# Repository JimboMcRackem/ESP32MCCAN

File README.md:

# ESP32 MCCAN

ESP32 motorcycle lighting controller. It reads the bike's CAN bus and drives 12 on/off outputs.
You configure it from a phone over its own Wi-Fi network.

The firmware is one image. `tools/embed_web.py` embeds the web app from `data/` at build time,
so there is no separate filesystem flash.

Settings and the Wi-Fi password live in NVS (namespace `mccan`). A legacy `/config.json` is
migrated once and then deleted, but only on a unit that still has the old partition table (see
below).

## Flashing over USB

Before the first USB flash of this firmware:

1. `python -m pip install cryptography` (needed by `tools/sign_update.py`).
2. `python tools/sign_update.py keygen`, then commit `src/domain/update_pubkey.h`. Firmware built
   with the all-zero placeholder key refuses every phone update until it is flashed over USB
   again.
3. Export your settings from the app's Backup tab. This firmware uses the `min_spiffs.csv`
   partition table (bigger app slots), so the old `/config.json` is not carried over. Import the
   backup after flashing.

```
PYTHONIOENCODING=utf-8 py -3.13 -m platformio run -e esp32 -t upload
```

This is the only flash. There is no `uploadfs`. Native tests run with `python -m platformio test -e native`.

The controller's Wi-Fi network is `MCCAN-XXXX` (XXXX is the last two bytes of the SoftAP MAC
address, which differs from the base MAC printed on module labels).
The default password is `mccan1234`, and the app nags until you change it.

## Releasing an update

1. Once only, before the first USB flash: `python tools/sign_update.py keygen`. The private key goes to `~/.mccan/update_key.pem`
   and the public half to `src/domain/update_pubkey.h`, which is built into the firmware.
   **Back up the key.** If it is lost, units in the field can only be updated over USB.
2. Bump `kBuildNumber` and `kVersionString` in `src/version.h`.
3. Build: `PYTHONIOENCODING=utf-8 py -3.13 -m platformio run -e esp32`
4. Sign:
   ```
   python tools/sign_update.py sign --key ~/.mccan/update_key.pem --bin .pio/build/esp32/firmware.bin --out mccan-<version>.mcup
   ```

The `.mcup` format is documented at the top of `tools/sign_update.py`.

## Installing an update from the phone

1. Join the `MCCAN-XXXX` network and open the app.
2. Go to the Device tab and choose the `.mcup` file.
3. The controller refuses an older build, and refuses any update while the bike is not parked.
4. After the update it restarts once the bike reads parked. The new image marks itself good
   after it has run for about 5 s with the Wi-Fi network up. If it crashes or is power-cycled
   before that, the next start goes back to the previous image. An image that hangs stays until
   a power cycle, and one that runs but behaves wrongly is kept: install a fixed update.

## Recovering a forgotten password

Factory reset: hold the reset button (GPIO0, labelled BOOT on the dev board) for 10 s while the
controller is running, then **release it within 5 s**. That erases the settings, and the
controller restarts with defaults (password `mccan1234`) as soon as the bike reads parked. A short
press does nothing. If the button is still held 5 s after the 10 s mark, the reset is cancelled;
release it and start a new 10 s hold to try again. The lamps keep working throughout.

Feedback: on the MCCAN board the status LED (GPIO13) fast-blinks at the 10 s mark (release now),
goes solid once the settings are erased, and goes off if cancelled. The dev board has no LED on
GPIO13: watch the serial log instead (`reset button held 10 s: release within 5 s ...`,
`factory reset: settings erased`).

Holding the button at power-up enters the ESP32's USB flashing mode instead. That is harmless.

## Bring-up notes

- On the dev board, a serial terminal that asserts DTR without RTS can hold GPIO0 low through the
  auto-program circuit. Held, it arms the reset at 10 s and cancels it at 15 s; it never erases
  unless the line is released inside that window. Use a monitor that leaves DTR and RTS
  deasserted.
- Hold BOOT through "Connecting......" if the upload cannot connect.

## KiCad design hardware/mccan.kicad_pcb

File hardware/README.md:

# MCCAN Hardware

KiCad 10.0.2 project for the ESP32 MCCAN lighting controller.
Spec: `../docs/superpowers/specs/2026-10-17-emarked-module-redesign-design.md`
Plan: `../docs/superpowers/plans/2026-10-18-board-schematic-phase-a.md`

## kicad-cli is not on PATH

Bash:       "/c/Program Files/KiCad/10.0/bin/kicad-cli.exe" <args>
PowerShell: & "C:\Program Files\KiCad\10.0\bin\kicad-cli.exe" <args>

## Verification gates

ERC applies to the current schematic. The DRC commands below apply to the abandoned plan3 board
until the layout phase produces a new one.

ERC (must exit 0):
  "/c/Program Files/KiCad/10.0/bin/kicad-cli.exe" sch erc \
    --severity-error --exit-code-violations \
    -o output/erc.rpt mccan.kicad_sch

DRC — run BOTH severities, and read the counts in the report body, not the exit code:

  "/c/Program Files/KiCad/10.0/bin/kicad-cli.exe" pcb drc \
    --severity-error --schematic-parity --exit-code-violations \
    --refill-zones -o output/drc.rpt mccan.kicad_pcb

  "/c/Program Files/KiCad/10.0/bin/kicad-cli.exe" pcb drc \
    --severity-all --schematic-parity --exit-code-violations \
    --refill-zones -o output/drc-all.rpt mccan.kicad_pcb

`--severity-error` alone is NOT the gate, and was the whole of it until Task 10. It discards
every finding whose rule sits at `warning`, and KiCad's stock project file puts 29 of its 62
rules there. On the board committed before `80fe282` that gate printed "Found 0 violations"
while `--severity-all` printed 28 — 15 `connection_width` and 13 `via_dangling`, one of the
`connection_width` findings a 0.059 mm neck at an eFuse gate pad. Every "DRC: 0 errors" on
this branch before that commit was measured through that filter.

`scripts/gen_netclasses.py` now promotes the seven rules that can fail THIS board to `error`
(see its `SEVERITIES`), so today the two runs agree. That agreement is a property of the
current KiCad rule set, not of the gate: a KiCad upgrade that adds a rule defaulting to
`warning` would make the `--severity-error` run blind again with no signal at all. Hence both.

Neither run's exit code is the pass/fail signal on its own — `kicad-cli` exits 5 whenever any
unconnected pad exists, and this board carries 11 accepted ones. The gate is the count in the
report body: it must match the accepted residual, currently 9 violations (all `via_dangling`),
11 unconnected pads, 0 footprint errors, at BOTH severities.

## Board setup decisions

Minimum connection width is 0.20 mm, tied to minimum track width.

  This section used to read "0.15 mm, not 0.25 mm ... minimum track width stays 0.25 mm",
  which was the six-layer board's setting and is three wrong figures now: both rules are
  0.20 mm today (`scripts/gen_netclasses.py`'s `RULES`, and `mccan.kicad_pro`).

  The two ARE tied on purpose. min_connection is the narrowest copper that may carry a
  connection, so setting it above the thinnest track the board permits makes every
  legitimately necked track a violation of a rule the same file grants -- two 0.20 mm
  tracks meeting at 45 degrees neck to 0.20 * cos(22.5) = 0.185 mm at the joint. The
  earlier note reached for the fabricator's limit instead, which is what the SCOPED
  plane-pour exception in `mccan.kicad_dru` is for, not what this rule is for. See the
  long `min_connection` note in `scripts/gen_netclasses.py`.

Reference designators are on F.Fab, except J*, F*, TP*, U*, Q*, D* and L*.

  233 parts on 140 x 100 mm leaves no room for 1 mm text: all 398 silkscreen warnings were
  Reference fields over a pad, over a neighbour's outline, or over another Reference, and
  none was between two real silk graphics.  Value was already on F.Fab, so the assembly
  drawing carries a fully labelled copy either way.  What stays on the silkscreen is what
  someone has to find on a finished board by eye -- connectors, fuses, test points and the
  semiconductors worth probing -- plus the outlines, pin-1 dots and polarity marks.

## Sheet responsibilities

| Sheet | Contents |
|---|---|
| power_input | Feed A (J1): LTC4380 U10 surge stopper with Q10/Q11 (no board fuse; the fuse is in the harness), 24 V TVS, pi + CM filter -> `VBAT`. Feed B (J9): SQJ461EP P-FET Q13 for reverse polarity, 15 V gate zener D24, 24 V TVS D25 -> `VBAT_B`, no filter, no LTC4380. `GND_B` (also the pods' return, out to the outputs sheet) meets `GND_IN` (the connector side of choke L2) only at net-tie NT1, so neither feed's return current bypasses L2's return winding |
| rails | Low-Iq buck -> `+3V3_ALW`, gated `+5V` (`EN_5V`). No boost and no `+3V3_SW` |
| mcu_can | ESP32-WROOM-32E, TJA1042T/3 (listen-only, TXD pulled up, no MCU link), programming header, 4.7 k series resistors on the diagnostic lines. GPIO 13 is `AUX_PWM` (the status LED is gone, 2026-11-13) |
| outputs | Three TPS4H160-Q1 quads U11-U13 (D1: 12 channels, 10 used, 2 spare), harness tails J3 (front, 5), J4 + J5 (rear, 4 + 3), CAN tail J8. Aux stage (2026-11-13): BTS7008-2EPA U14 switches both pods from `VBAT_B`, 74AHCT2G126DC U15 buffers `AUX_PWM` to each yellow (enabled only while that pod is powered), pod tails J10/J11. See `docs/superpowers/specs/2026-11-13-aux-stage-design.md` |

The pin map and net names are the generators' (`scripts/gen_*.py`, `scripts/quadpins.py`) and the
netlist `output/netlist.net`. The plan3 pin tables that used to be here (PCA9685, mux, ignition
sense, PWM nets) described a board that no longer exists and have been removed.

### ESP32 pin rules that still hold

- GPIO 6-11 are the module's flash and are unusable. GPIO 37 and 38 are not bonded out.
- GPIO 34-39 are input-only and have **no internal pulls**. Here: 34 `SNS_A`, 35 `CAN_RXD`
  (RTC, EXT1 wake), 36 `SNS_B`, 39 `SNS_C`.
- ADC2 fails while Wi-Fi is up, so the sense inputs are all ADC1.
- Strapping pins, and what this board ties them to:
  - GPIO 0 is `BOOT_N`: the BOOT button SW1 and the auto-reset transistor Q3.
  - GPIO 2 is `DIAG_EN`: 4.7 k series, with R33 47 k pull-down on the chip side. It must be low
    for download, and the same pull-down holds the switches' `DIAG_EN` low. High level: 47 k ∥ 33.3 k
    (three chips at 100 k min) = 19.5 k, so 3.3 × 19.5 / (19.5 + 4.7) = 2.66 V against VIH 2.0 V.
  - GPIO 5 and 15 are `DIAG_SEL0` / `DIAG_SEL1`: 4.7 k series, **no pull** (their level is
    irrelevant while `DIAG_EN` is low). The three SEH internal pull-downs (100 k min each) load
    GPIO 15 against its internal pull-up, so the ROM boot log will probably be muted; that is
    harmless. Optional fix: a 10 k pull-up on the MCU side of R32 (not fitted).
  - GPIO 12 is `IO12_STRAP`: R36 10 k to GND (flash voltage select; also the firmware's TWAI TX pin).
- No lamp output sits on a strapping pin or on GPIO 14.

## Phase-A board status (2026-10-18)

The **schematic** is complete except the kit-gated aux/pod switch. The **layout has not started**.

- `mccan.kicad_pcb` and `output/gerbers/` are the **abandoned plan3 board**. They no longer match
  the schematic and must not be fabricated or used as a layout starting point. The DRC commands
  and counts under "Verification gates" describe that board.
- `scripts/layout_*.py` and `scripts/route_*` (also `routes_signal.json`) still reference plan3
  parts that phase A deleted -- `layout_pcb.py` lists refs such as U7, U8, U9, J6 and J7 -- and
  must be reworked in the layout phase. Do not run them, or `gen_pcb.py`, until then.

### Layout-phase notes

- **U10 (LTC4380) `ON` is deliberately left open** on its internal 1 Mohm pull-up. The layout must
  keep that pin's leakage to ground under 1 uA (LTC4380 Rev. C, Pin Functions): no flux-prone
  gap, guard or close ground copper beside the pad.
- `NT1` is the deliberate `GND_B` / `GND_IN` star point (connector side of L2, so no return current bypasses L2's return winding); place it deliberately (spec §4.1.1). It is a 2.0 mm tie so it outlasts the harness fuse when one feed is reversed while the other is connected.

### Phase-A bring-up checklist (additions)

- **ROM boot log may be absent.** The three SEH internal pull-downs load GPIO 15 (MTDO), so the boot ROM log is probably muted. Harmless. Optional fix: a 10 k pull-up on the MCU side of R32 (not fitted).
- **GPIO12 / flash voltage.** TWAI holds GPIO12 (the MTDI strap) high while running. R36 makes every reset safe. The optional permanent remedy is `espefuse.py set_flash_voltage 3.3V`, which is **IRREVERSIBLE** and is the owner's decision; it has not been run.
- **Diagnostics settling.** After any `DIAG_SEL` or `DIAG_EN` change wait >= 400 us before reading `SNS_x`.
- **Reverse polarity.** Test one feed reversed with the other disconnected, and the whole harness reversed. Test one feed reversed with the other connected only on a current-limited bench supply: that drives fault current through NT1 and the shared return until the harness fuse clears.
- `R100` sets about 9 A behind a 4 A fuse and is re-sized once pod inrush is measured (spec §9.1 item 2a).

> The two sections below, "Project status (Task 1)" and the 2026-09-11 revision, are plan3 history
> kept for the record; the phase-A status above supersedes them.

## Project status (Task 1)

Hierarchical sheets ARE wired: the root schematic (`mccan.kicad_sch`) places four
`(sheet ...)` instances (`power_input`, `rails`, `mcu_can`, `outputs`), each pointing at
its file under `sheets/`. This was authored as text — no KiCad GUI session was available —
and verified structurally sound by running `kicad-cli sch erc`, whose report walked into
all four child sheets (`Sheet /power_input/`, `Sheet /mcu_can/`, `Sheet /rails/`,
`Sheet /outputs/`) with 0 errors. No components are placed on any sheet yet; that begins
in Task 3.

There is no `mccan.kicad_pcb` yet, so the DRC gate above cannot be run until PCB layout
(Task 8) creates one. The command is documented here now because the net naming and
sheet contracts it will check are fixed as of this task.

## Verified gate: ERC (Task 1, empty project)

Command:
```
cd hardware && "/c/Program Files/KiCad/10.0/bin/kicad-cli.exe" sch erc \
  --severity-error --exit-code-violations -o output/erc.rpt mccan.kicad_sch
```

Result: `exit=0`, "Found 0 violations". Report saved at `output/erc.rpt`. This is expected
at this stage — it proves the gate command and the hierarchical project structure work,
not that any design is correct (there is no design yet).

## REVISION 2026-09-11 — RGB output stage redesigned

Datasheet verification failed the octal smart low-side switches: ON-state open-load detection does
not exist in that part category (TLE8110ED's open-load code is OFF-mode only, and it is a VDS
comparator with no load-current threshold at all). The RGB stage is now:

- **12 discrete logic-level N-MOSFETs**, gates driven straight from PCA9685 LED0-11
- **1 ohm shunt in each FET source leg** -> 12 `SENSE_*` nets
- **16:1 analog mux** (`MUX_S0`-`S3`) -> `RGB_ISNS` -> GPIO 32 (ADC1_CH4)
- 140 mV at full channel current; ADC at 0 dB attenuation (0-1.1 V range)
- Classification is open / working / shorted, not precision metering
- Sampling is on-demand: drive a channel to 100%, step the mux, read, advance

**There is no SPI on this board** — the switch ICs were its only devices. Dropping it freed the
GPIO that made the sense chain fit.

**A 5 V rail is mandatory**: TJA1042 VCC is 4.5-5.5 V. The "/3" suffix provides VIO for 3.3 V logic
levels; it does not make VCC 3.3 V. **It is ENABLE-GATED off in sleep**, sharing `EN_3V3SW` with
`+3V3_SW` — the transceiver's low-power receiver detects bus activity on **VIO alone**, so VCC is
needed only for normal mode. VIO stays on `+3V3_ALW`.

Authority: `../docs/superpowers/specs/2026-09-11-esp32-mccan-pcb-hardware-design.md` sections 5.1,
6 and 7.3.

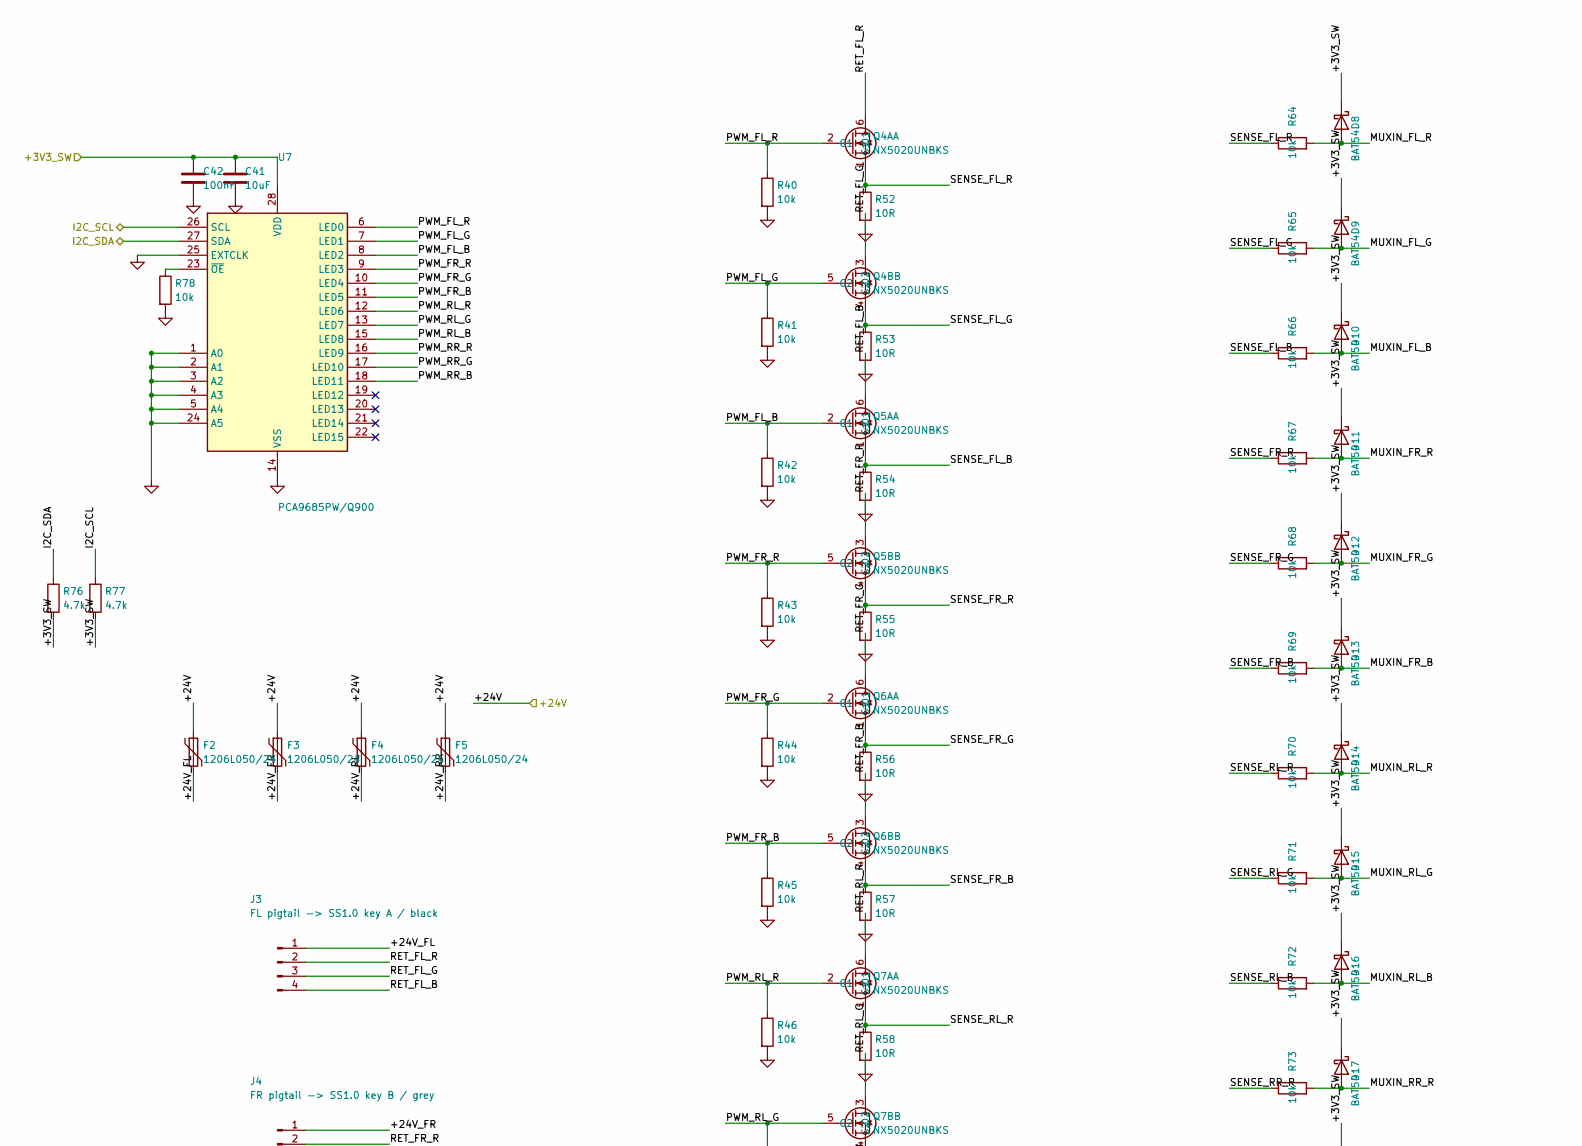
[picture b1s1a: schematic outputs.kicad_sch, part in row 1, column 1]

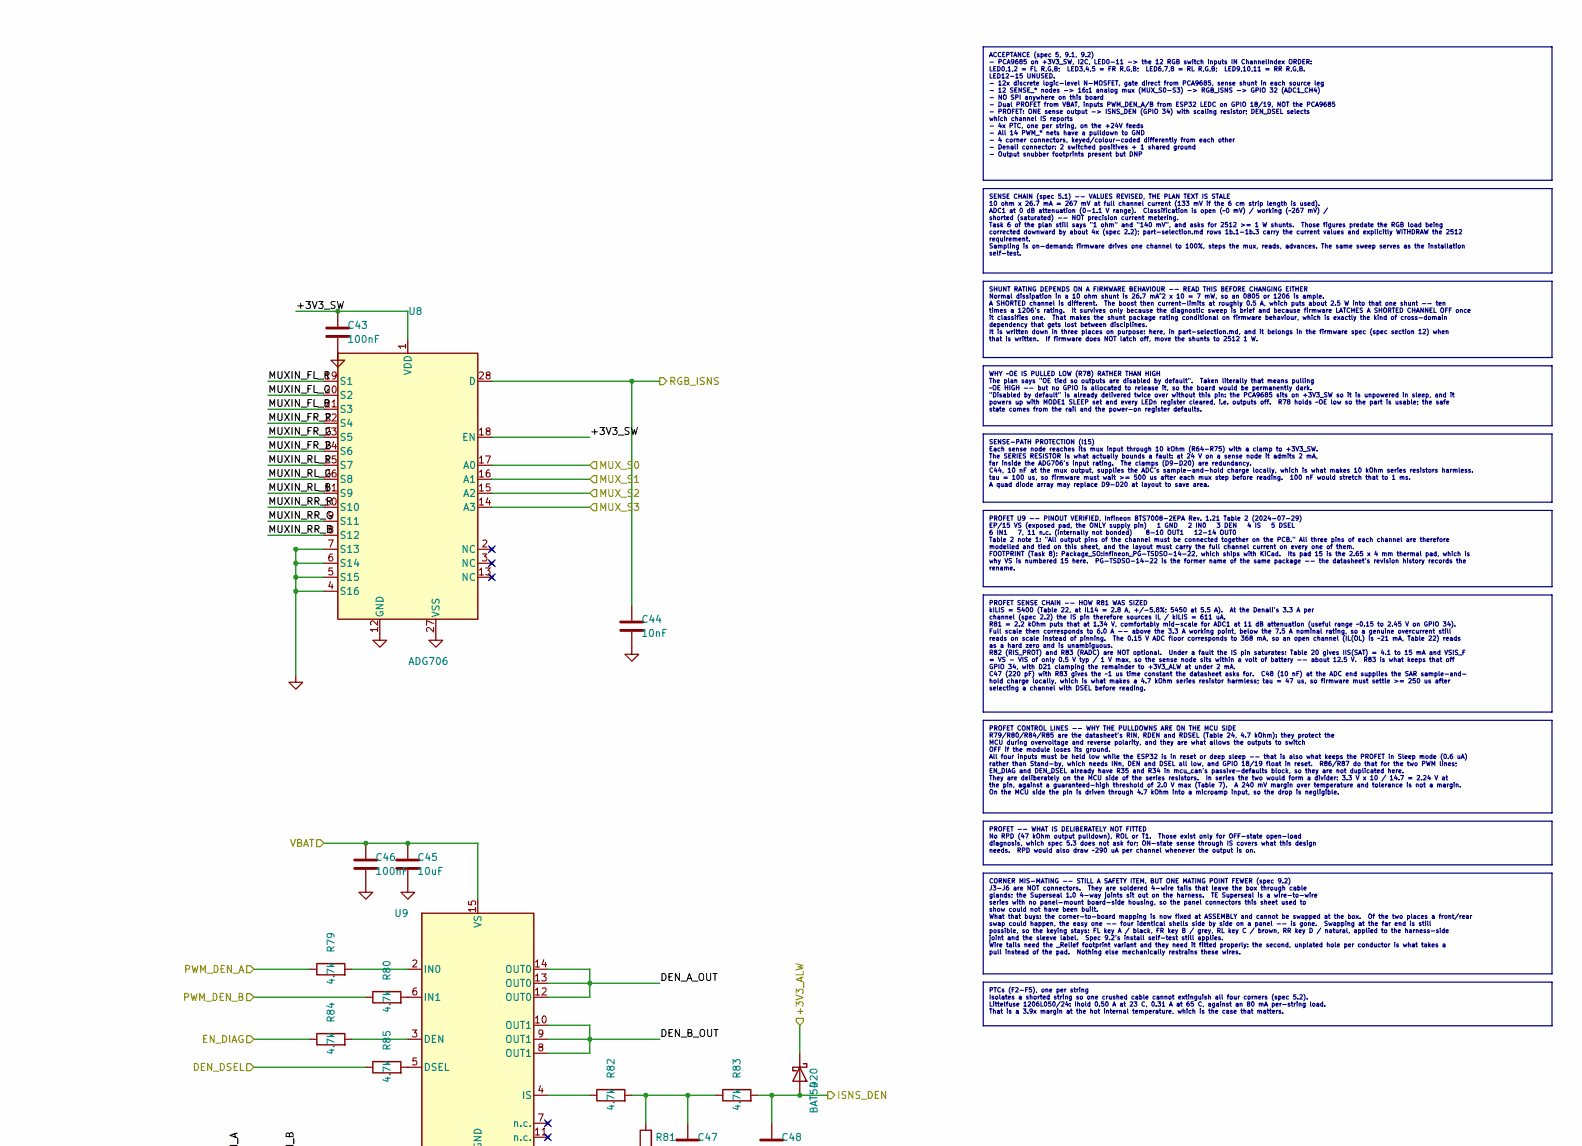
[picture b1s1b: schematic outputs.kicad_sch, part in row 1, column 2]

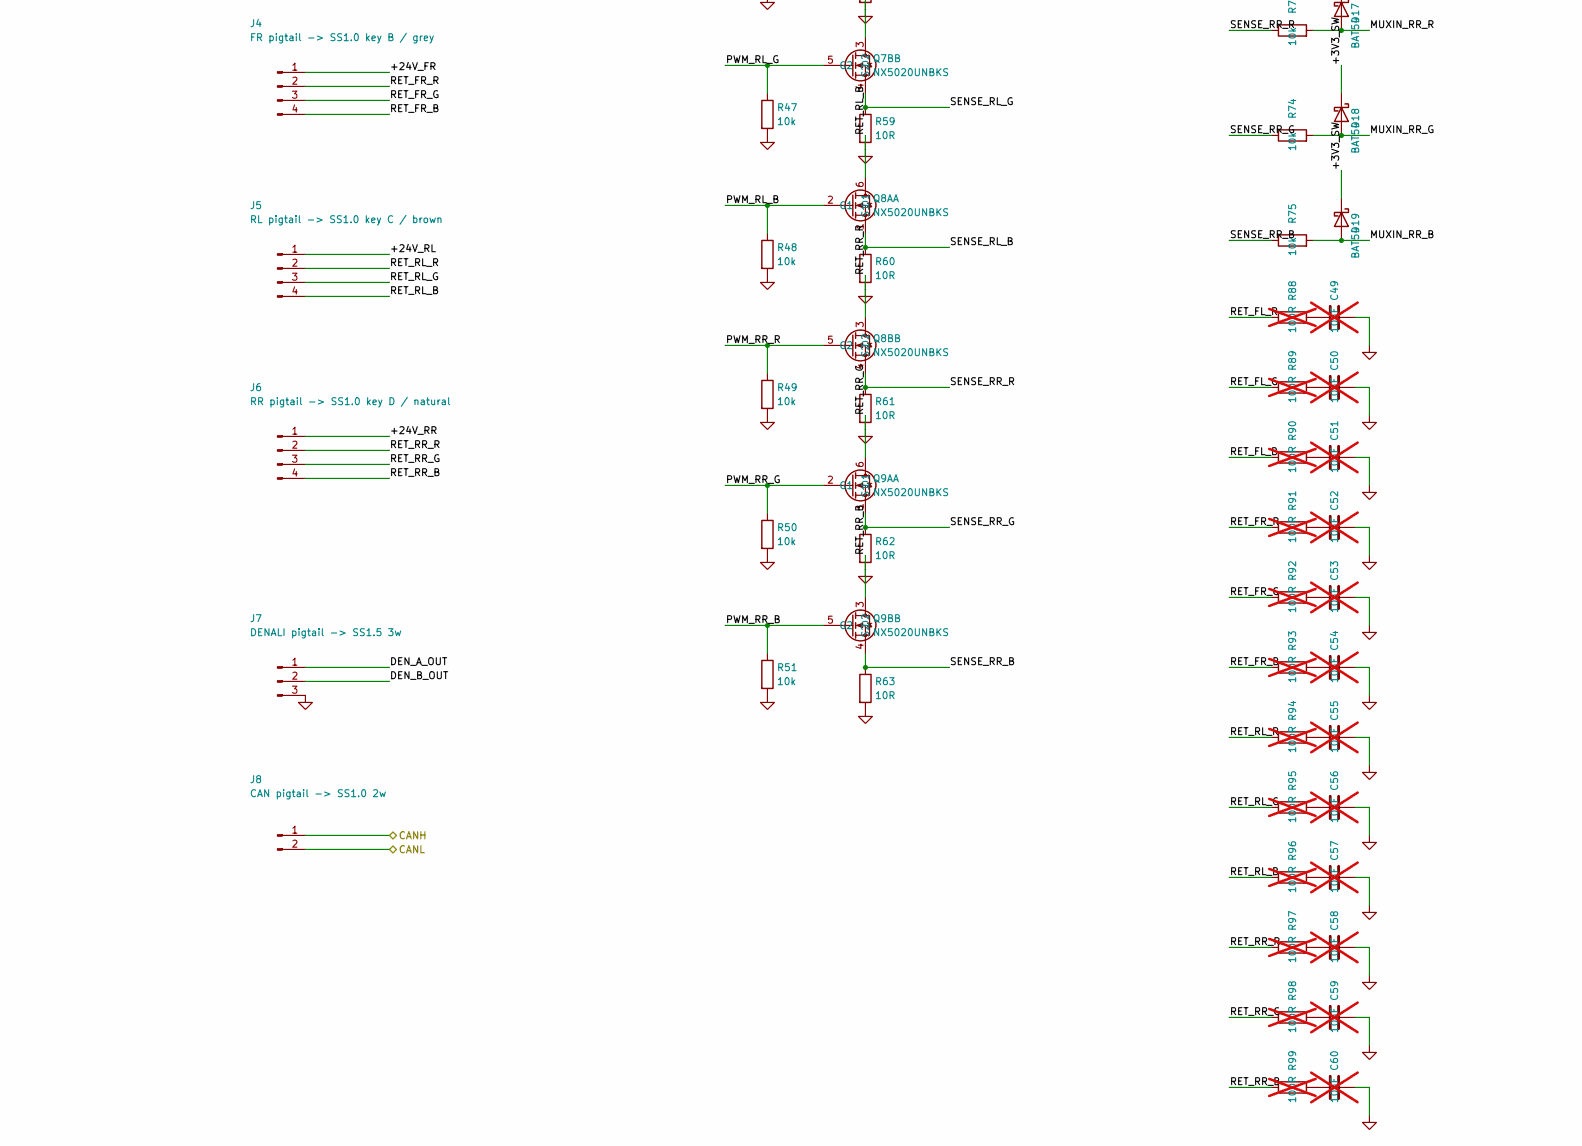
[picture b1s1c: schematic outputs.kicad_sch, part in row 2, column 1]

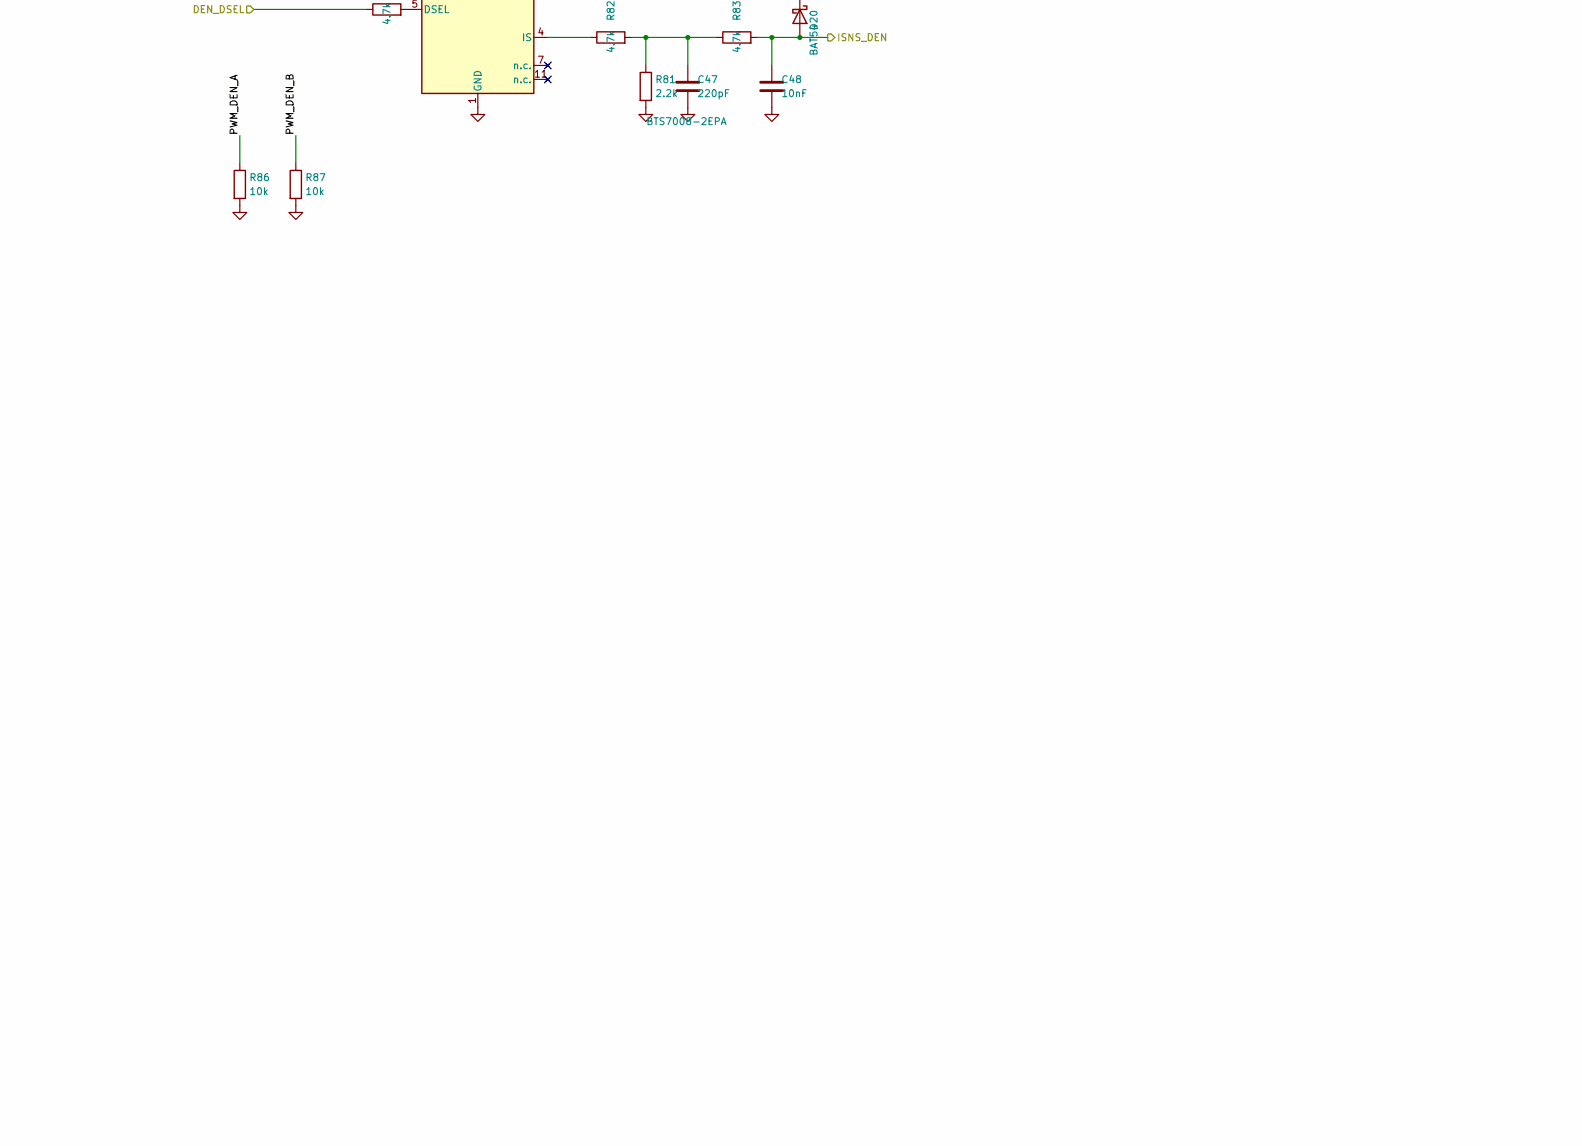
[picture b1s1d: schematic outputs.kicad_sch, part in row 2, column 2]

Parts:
C41: 10uF; C_0603_1608Metric
C42, C43: 100nF; C_0603_1608Metric
C44, C48: 10nF; C_0603_1608Metric
C45: 10uF; C_1210_3225Metric
C46: 100nF; C_0805_2012Metric
C47: 220pF; C_0603_1608Metric
C49, C50, C51, C52, C53, C54, C55, C56, C57, C58, C59, C60: 10nF; C_1206_3216Metric; not fitted
D8, D9, D10, D11, D12, D13, D14, D15, D16, D17, D18, D19, D20: BAT54; D_SOD-123
F2, F3, F4, F5: 1206L050/24; Fuse_1206_3216Metric
J3: FL pigtail -> SS1.0 key A / black; SolderWire-0.5sqmm_1x04_P4.6mm_D0.9mm_OD2.1mm_Relief
J4: FR pigtail -> SS1.0 key B / grey; SolderWire-0.5sqmm_1x04_P4.6mm_D0.9mm_OD2.1mm_Relief
J5: RL pigtail -> SS1.0 key C / brown; SolderWire-0.5sqmm_1x04_P4.6mm_D0.9mm_OD2.1mm_Relief
J6: RR pigtail -> SS1.0 key D / natural; SolderWire-0.5sqmm_1x04_P4.6mm_D0.9mm_OD2.1mm_Relief
J7: DENALI pigtail -> SS1.5 3w; SolderWire-1.5sqmm_1x03_P6mm_D1.7mm_OD3mm_Relief
J8: CAN pigtail -> SS1.0 2w; SolderWire-0.5sqmm_1x02_P4.6mm_D0.9mm_OD2.1mm_Relief
Q4A, Q4B, Q5A, Q5B, Q6A, Q6B, Q7A, Q7B, Q8A, Q8B, Q9A, Q9B: NX5020UNBKS; SOT-363_SC-70-6
R40, R41, R42, R43, R44, R45, R46, R47, R48, R49, R50, R51, R64, R65, R66, R67, R68, R69, R70, R71, R72, R73, R74, R75, R78, R86, R87: 10k; R_0603_1608Metric
R52, R53, R54, R55, R56, R57, R58, R59, R60, R61, R62, R63: 10R; R_1206_3216Metric
R76, R77, R79, R80, R82, R83, R84, R85: 4.7k; R_0603_1608Metric
R81: 2.2k; R_0603_1608Metric
R88, R89, R90, R91, R92, R93, R94, R95, R96, R97, R98, R99: 100R; R_1206_3216Metric; not fitted
U7: PCA9685PW/Q900; TSSOP-28_4.4x9.7mm_P0.65mm
U8: ADG706; TSSOP-28_4.4x9.7mm_P0.65mm
U9: BTS7008-2EPA; Infineon_PG-TSDSO-14-22

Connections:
/+3V3_ALW: D20.1 (K); also elsewhere on the board
/+3V3_SW: C41.1, C42.1, C43.1, D8.1 (K), D9.1 (K), D10.1 (K), D11.1 (K), D12.1 (K), D13.1 (K), D14.1 (K), D15.1 (K), D16.1 (K), D17.1 (K), D18.1 (K), D19.1 (K), R76.2, R77.2, U7.28 (VDD), U8.1 (VDD), U8.18 (EN); also elsewhere on the board
/+24V: F2.1, F3.1, F4.1, F5.1; also elsewhere on the board
/CANH: J8.1; also elsewhere on the board
/CANL: J8.2; also elsewhere on the board
/DEN_DSEL: R85.1; also elsewhere on the board
/EN_DIAG: R84.1; also elsewhere on the board
/I2C_SCL: R77.1, U7.26 (SCL); also elsewhere on the board
/I2C_SDA: R76.1, U7.27 (SDA); also elsewhere on the board
/ISNS_DEN: C48.1, D20.2 (A), R83.2; also elsewhere on the board
/MUX_S0: U8.17 (A0); also elsewhere on the board
/MUX_S1: U8.16 (A1); also elsewhere on the board
/MUX_S2: U8.15 (A2); also elsewhere on the board
/MUX_S3: U8.14 (A3); also elsewhere on the board
/PWM_DEN_A: R79.1, R86.1; also elsewhere on the board
/PWM_DEN_B: R80.1, R87.1; also elsewhere on the board
/RGB_ISNS: C44.1, U8.28 (D); also elsewhere on the board
/VBAT: C45.1, C46.1, U9.15 (VS); also elsewhere on the board
/outputs/+24V_FL: F2.2, J3.1
/outputs/+24V_FR: F3.2, J4.1
/outputs/+24V_RL: F4.2, J5.1
/outputs/+24V_RR: F5.2, J6.1
/outputs/DEN_A_OUT: J7.1, U9.12 (OUT0), U9.13 (OUT0), U9.14 (OUT0)
/outputs/DEN_B_OUT: J7.2, U9.8 (OUT1), U9.9 (OUT1), U9.10 (OUT1)
/outputs/MUXIN_FL_B: D10.2 (A), R66.2, U8.21 (S3)
/outputs/MUXIN_FL_G: D9.2 (A), R65.2, U8.20 (S2)
/outputs/MUXIN_FL_R: D8.2 (A), R64.2, U8.19 (S1)
/outputs/MUXIN_FR_B: D13.2 (A), R69.2, U8.24 (S6)
/outputs/MUXIN_FR_G: D12.2 (A), R68.2, U8.23 (S5)
/outputs/MUXIN_FR_R: D11.2 (A), R67.2, U8.22 (S4)
/outputs/MUXIN_RL_B: D16.2 (A), R72.2, U8.11 (S9)
/outputs/MUXIN_RL_G: D15.2 (A), R71.2, U8.26 (S8)
/outputs/MUXIN_RL_R: D14.2 (A), R70.2, U8.25 (S7)
/outputs/MUXIN_RR_B: D19.2 (A), R75.2, U8.8 (S12)
/outputs/MUXIN_RR_G: D18.2 (A), R74.2, U8.9 (S11)
/outputs/MUXIN_RR_R: D17.2 (A), R73.2, U8.10 (S10)
/outputs/PWM_FL_B: R42.1, U7.8 (LED2); also elsewhere on the board
/outputs/PWM_FL_G: R41.1, U7.7 (LED1); also elsewhere on the board
/outputs/PWM_FL_R: R40.1, U7.6 (LED0); also elsewhere on the board
/outputs/PWM_FR_B: R45.1, U7.11 (LED5); also elsewhere on the board
/outputs/PWM_FR_G: R44.1, U7.10 (LED4); also elsewhere on the board
/outputs/PWM_FR_R: R43.1, U7.9 (LED3); also elsewhere on the board
/outputs/PWM_RL_B: R48.1, U7.15 (LED8); also elsewhere on the board
/outputs/PWM_RL_G: R47.1, U7.13 (LED7); also elsewhere on the board
/outputs/PWM_RL_R: R46.1, U7.12 (LED6); also elsewhere on the board
/outputs/PWM_RR_B: R51.1, U7.18 (LED11); also elsewhere on the board
/outputs/PWM_RR_G: R50.1, U7.17 (LED10); also elsewhere on the board
/outputs/PWM_RR_R: R49.1, U7.16 (LED9); also elsewhere on the board
/outputs/RET_FL_R: J3.2, R88.1; also elsewhere on the board
/outputs/SENSE_FL_B: R54.1, R66.1; also elsewhere on the board
/outputs/SENSE_FL_G: R53.1, R65.1; also elsewhere on the board
/outputs/SENSE_FL_R: R52.1, R64.1; also elsewhere on the board
/outputs/SENSE_FR_B: R57.1, R69.1; also elsewhere on the board
/outputs/SENSE_FR_G: R56.1, R68.1; also elsewhere on the board
/outputs/SENSE_FR_R: R55.1, R67.1; also elsewhere on the board
/outputs/SENSE_RL_B: R60.1, R72.1; also elsewhere on the board
/outputs/SENSE_RL_G: R59.1, R71.1; also elsewhere on the board
/outputs/SENSE_RL_R: R58.1, R70.1; also elsewhere on the board
/outputs/SENSE_RR_B: R63.1, R75.1; also elsewhere on the board
/outputs/SENSE_RR_G: R62.1, R74.1; also elsewhere on the board
/outputs/SENSE_RR_R: R61.1, R73.1; also elsewhere on the board
unnamed: C47.1, R81.1, R82.2, R83.1
unnamed: C49.1, R88.2
unnamed: C50.1, R89.2
unnamed: C51.1, R90.2
unnamed: C52.1, R91.2
unnamed: C53.1, R92.2
unnamed: C54.1, R93.2
unnamed: C55.1, R94.2
unnamed: C56.1, R95.2
unnamed: C57.1, R96.2
unnamed: C58.1, R97.2
unnamed: C59.1, R98.2
unnamed: C60.1, R99.2
unnamed: R78.1, U7.23 (~OE)
unnamed: R84.2, U9.3 (DEN)
unnamed: R85.2, U9.5 (DSEL)
unnamed: R79.2, U9.2 (IN0)
unnamed: R80.2, U9.6 (IN1)
unnamed: R82.1, U9.4 (IS)

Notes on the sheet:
PROFET U9 -- PINOUT VERIFIED, Infineon BTS7008-2EPA Rev. 1.21 Table 2 (2024-07-29) EP/15 VS (exposed pad, the ONLY supply pin) 1 GND 2 IN0 3 DEN 4 IS 5 DSEL 6 IN1 7, 11 n.c. (internally not bonded) 8-10 OUT1 12-14 OUT0 Table 2 note 1: "All output pins of the channel must be connected together on th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
PTCs (F2-F5), one per string Isolates a shorted string so one crushed cable cannot extinguish all four corners (spec 5.2). Littelfuse 1206L050/24: Ihold 0.50 A at 23 C, 0.31 A at 65 C, against an 80 mA per-string load. That is a 3.9x margin at the hot internal temperature, which is the case that ma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
PROFET SENSE CHAIN -- HOW R81 WAS SIZED kILIS = 5400 (Table 22, at IL14 = 2.8 A, +/-5.8%; 5450 at 5.5 A). At the Denali's 3.3 A per channel (spec 2.2) the IS pin therefore sources IL / kILIS = 611 uA. R81 = 2.2 kOhm puts that at 1.34 V, comfortably mid-scale for ADC1 at 11 dB attenuation (useful ra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
CORNER MIS-MATING -- STILL A SAFETY ITEM, BUT ONE MATING POINT FEWER (spec 9.2) J3-J6 are NOT connectors. They are soldered 4-wire tails that leave the box through cable glands; the Superseal 1.0 4-way joints sit out on the harness. TE Superseal is a wire-to-wire series with no panel-mount board-si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
SENSE-PATH PROTECTION (I15) Each sense node reaches its mux input through 10 kOhm (R64-R75) with a clamp to +3V3_SW. The SERIES RESISTOR is what actually bounds a fault: at 24 V on a sense node it admits 2 mA, far inside the ADG706's input rating. The clamps (D9-D20) are redundancy. C44, 10 nF at t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
ACCEPTANCE (spec 5, 9.1, 9.2) - PCA9685 on +3V3_SW, I2C, LED0-11 -> the 12 RGB switch inputs IN ChannelIndex ORDER: LED0,1,2 = FL R,G,B; LED3,4,5 = FR R,G,B; LED6,7,8 = RL R,G,B; LED9,10,11 = RR R,G,B. LED12-15 UNUSED. - 12x discrete logic-level N-MOSFET, gate direct from PCA9685, sense shunt in ea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
SENSE CHAIN (spec 5.1) -- VALUES REVISED, THE PLAN TEXT IS STALE 10 ohm x 26.7 mA = 267 mV at full channel current (133 mV if the 6 cm strip length is used). ADC1 at 0 dB attenuation (0-1.1 V range). Classification is open (~0 mV) / working (~267 mV) / shorted (saturated) -- NOT precision current m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
SHUNT RATING DEPENDS ON A FIRMWARE BEHAVIOUR -- READ THIS BEFORE CHANGING EITHER Normal dissipation in a 10 ohm shunt is 26.7 mA^2 x 10 = 7 mW, so an 0805 or 1206 is ample. A SHORTED channel is different. The boost then current-limits at roughly 0.5 A, which puts about 2.5 W into that one shunt -- 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
WHY ~OE IS PULLED LOW (R78) RATHER THAN HIGH The plan says "OE tied so outputs are disabled by default". Taken literally that means pulling ~OE HIGH -- but no GPIO is allocated to release it, so the board would be permanently dark. "Disabled by default" is already delivered twice over without this 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
PROFET CONTROL LINES -- WHY THE PULLDOWNS ARE ON THE MCU SIDE R79/R80/R84/R85 are the datasheet's RIN, RDEN and RDSEL (Table 24, 4.7 kOhm): they protect the MCU during overvoltage and reverse polarity, and they are what allows the outputs to switch OFF if the module loses its ground. All four input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
PROFET -- WHAT IS DELIBERATELY NOT FITTED No RPD (47 kOhm output pulldown), ROL or T1. Those exist only for OFF-state open-load diagnosis, which spec 5.3 does not ask for; ON-state sense through IS covers what this design needs. RPD would also draw ~290 uA per channel whenever the output is on.
